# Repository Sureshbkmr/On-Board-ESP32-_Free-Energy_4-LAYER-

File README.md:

# On-Board-ESP32-_Free-Energy_4-LAYER-
A professional 4-layer motor driver PCB using ESP32 designed in KiCad

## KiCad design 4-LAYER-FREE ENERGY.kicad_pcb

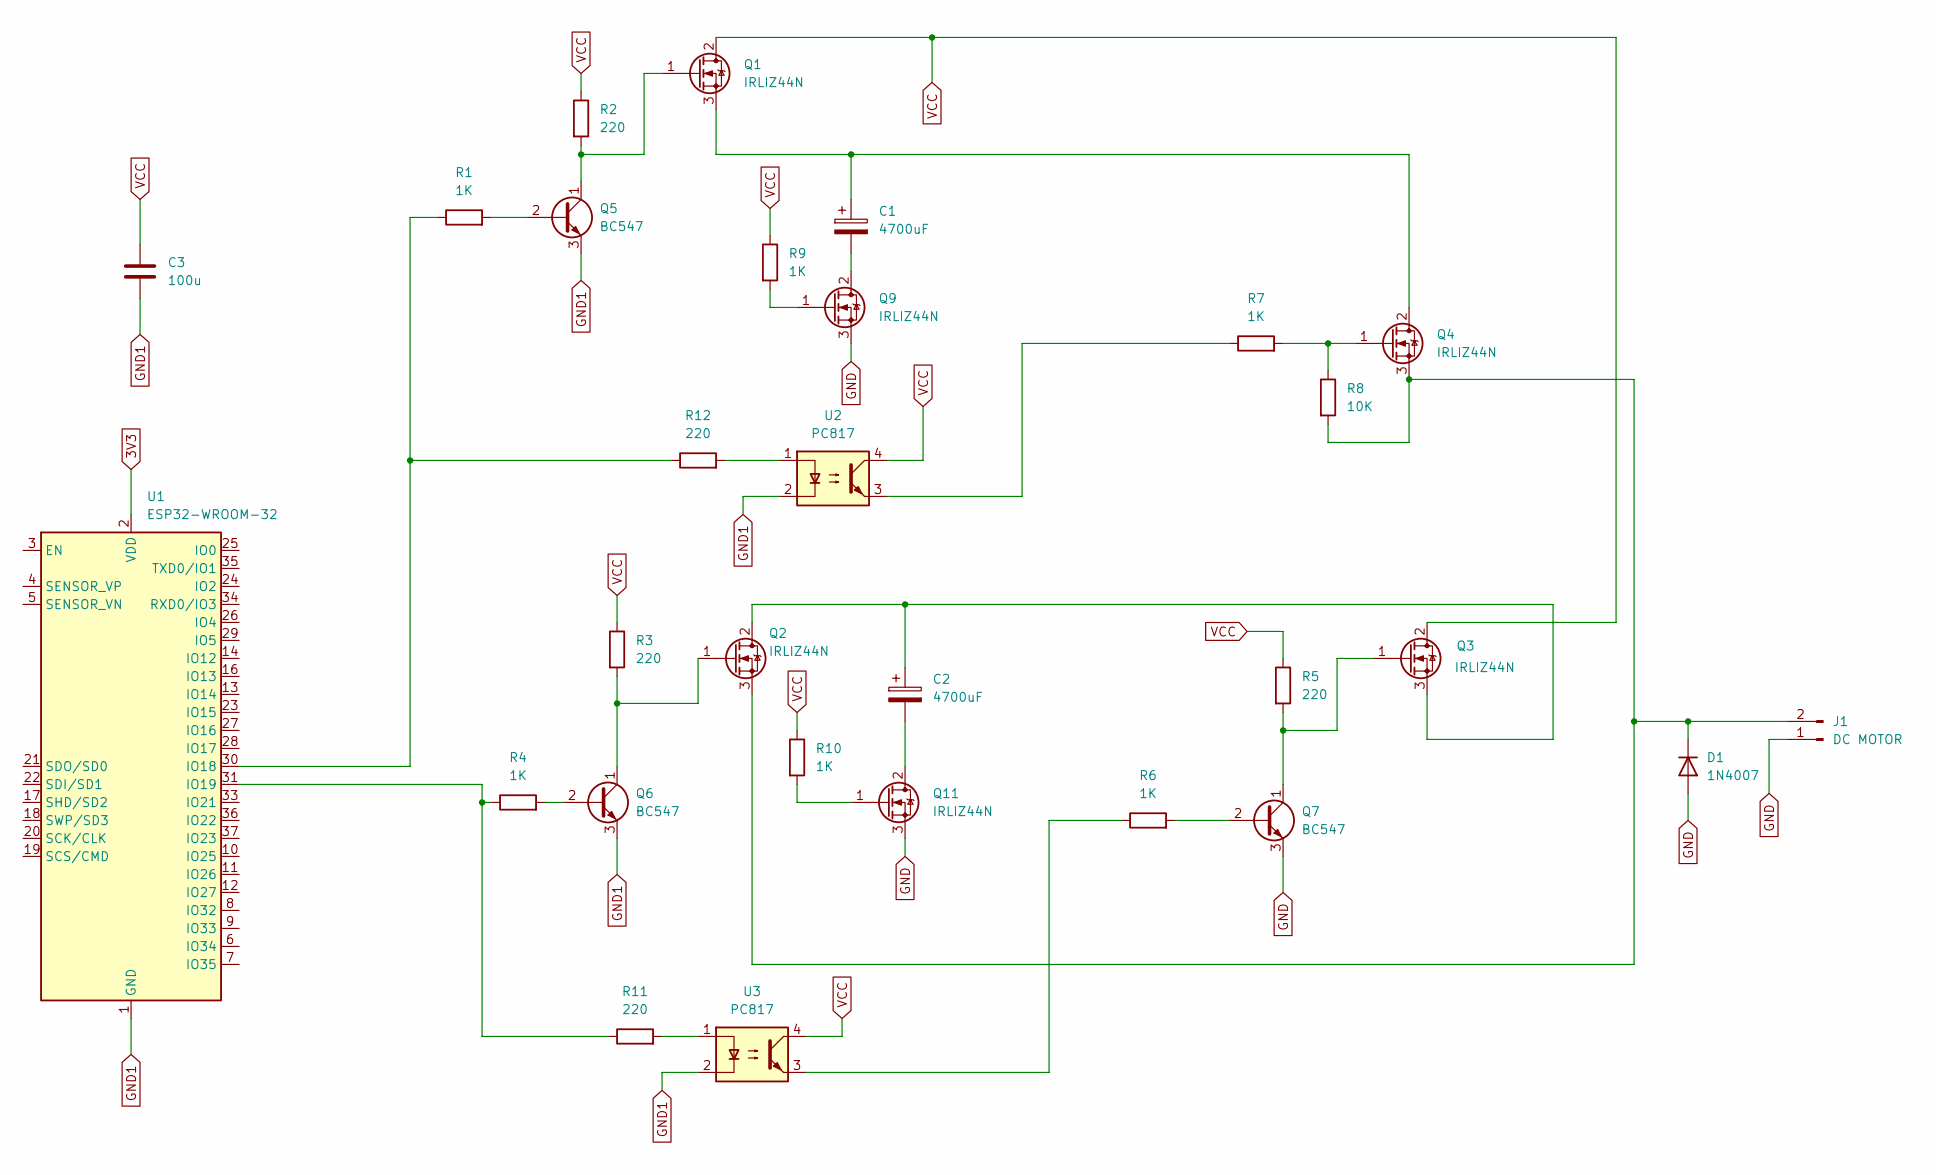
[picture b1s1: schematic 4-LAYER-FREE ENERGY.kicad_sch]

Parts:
C1, C2: 4700uF; CP_Elec_8x10.5
C3: 100u; C_0805_2012Metric
D1: 1N4007; D_DO-41_SOD81_P10.16mm_Horizontal
J1: DC MOTOR; PinHeader_1x02_P2.54mm_Vertical
Q1, Q2, Q3, Q4, Q9, Q11: IRLIZ44N; TO-220F-3_Vertical
Q5, Q6, Q7: BC547; TO-92_Inline
R1, R4, R6, R7, R9, R10: 1K; R_0805_2012Metric
R2, R3, R5, R11, R12: 220; R_0805_2012Metric
R8: 10K; R_0805_2012Metric
U1: ESP32-WROOM-32
U2, U3: PC817; DIP-4_W7.62mm

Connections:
3V3: U1.2 (VDD)
GND: D1.2 (A), J1.1, Q7.3 (E), Q9.3 (S), Q11.3 (S)
GND1: C3.2, Q5.3 (E), Q6.3 (E), U1.1 (GND), U1.15 (GND), U1.38 (GND), U1.39 (GND), U2.2, U3.2
unnamed: D1.1 (K), J1.2, Q2.3 (S), Q4.3 (S), R8.2
unnamed: Q1.1 (G), Q5.1 (C), R2.2
unnamed: C1.1, Q1.3 (S), Q4.2 (D)
unnamed: C2.1, Q2.2 (D), Q3.3 (S)
unnamed: Q2.1 (G), Q6.1 (C), R3.2
unnamed: Q3.1 (G), Q7.1 (C), R5.2
unnamed: Q4.1 (G), R7.2, R8.1
unnamed: Q5.2 (B), R1.2
unnamed: Q6.2 (B), R4.2
unnamed: Q7.2 (B), R6.2
unnamed: C1.2, Q9.2 (D)
unnamed: Q9.1 (G), R9.2
unnamed: C2.2, Q11.2 (D)
unnamed: Q11.1 (G), R10.2
unnamed: R6.1, U3.3
unnamed: R7.1, U2.3
unnamed: R11.2, U3.1
unnamed: R12.2, U2.1
unnamed: R1.1, R12.1, U1.30 (IO18)
unnamed: R4.1, R11.1, U1.31 (IO19)
VCC: C3.1, Q1.2 (D), Q3.2 (D), R2.1, R3.1, R5.1, R9.1, R10.1, U2.4, U3.4

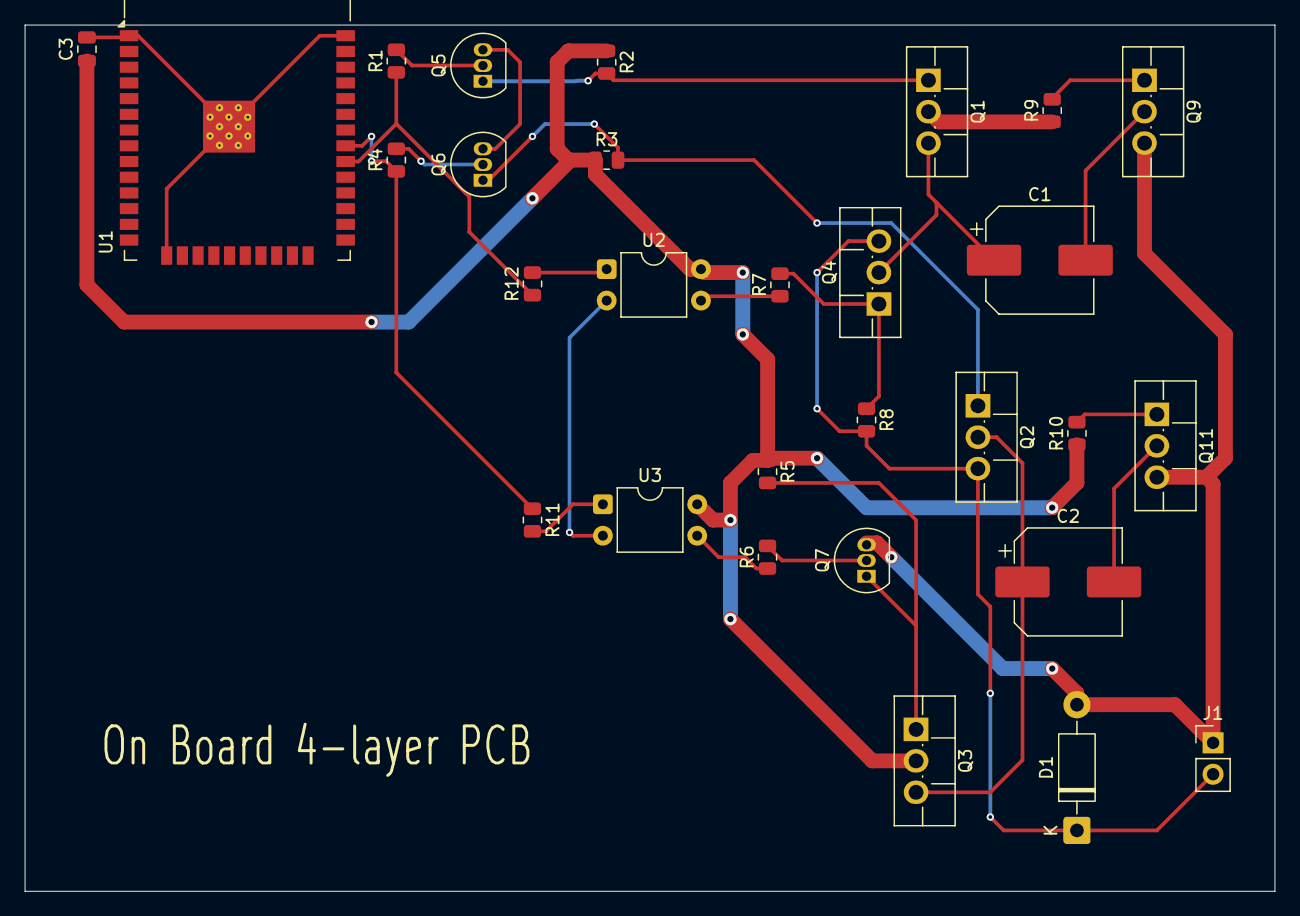
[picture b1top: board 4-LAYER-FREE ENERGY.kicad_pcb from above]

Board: 4 copper layers, 101.0 x 70.0 mm, 29 parts (0 on the bottom side), 23 nets.
